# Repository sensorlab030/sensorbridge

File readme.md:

# Sensor Bridge

The sensor bridge board is a small piece of embedded hardware that allows the 
user to easily connect up to six analog sensors. The board will then read the 
data from the sensors and send this data via the serial port to a [client 
application](https://github.com/sensorlab030/sensorbridge-client) which then
either records the data to files or serves it over a websocket to interested
applications.

The firmware (/firmware) of the sensor board is [Arduino](https://www.arduino.cc/) 
based and the board layout files (/hardware) are created with 
[CadSoft/Autodesk Eagle](http://www.autodesk.com/products/eagle/overview)

## Protocol

The data from the sensors is sent over the serial port at a baud rate of 9600 
bps. 

The serial protocol in which the data is communicated is very straighforward: 
it will always send six two-byte (16 bit) values (ordered from sensor one to 
sensor six), separated by a carriage return (```0x0D```) and a line feed 
(```0x0A```). So one single message will always be 14 bytes long and  be ordered 
like this:

```
Sensor 1 value | Sensor 2 value | Sensor 3 value | Sensor 4 value |
Sensor 5 value | Sensor 5 value | Carriage return | Line feed
```

The sensor readings will have a value from 0 to 1023 (10 bit), and will be 
sent with the high byte first. If it is detected that there is no sensor 
connected to the analog input, a value of ```FF:FF``` will be sent to notify the 
disconnected state of the sensor.

### Example 1: One sensor connected, analog value of 0

This is the message that is sent when only the first sensor is connected that
has a sensor reading of 0 (```00:00```).

```
00:00:FF:FF:FF:FF:FF:FF:FF:FF:FF:FF:0D:0A
```

### Example 2: One sensor connected, analog value of 1023

This is the message that is sent when only the first sensor is connected that
has a sensor reading of 1023 (```03:FF```).

```
03:FF:FF:FF:FF:FF:FF:FF:FF:FF:FF:FF:0D:0A
```

## License

The firmware (everything under /firmware) is licensed under the GPLv3, the 
Arduino core libraries and IDE are under their own respective licenses (GNU 
LGPL and GNU GPL). License text can be found under /firmware/license.txt

The board layout files (everything under /hardware) is under the Creative 
Commons Attribution-ShareAlike 3.0 Unported License. License text can be 
found under /hardware/license.txt

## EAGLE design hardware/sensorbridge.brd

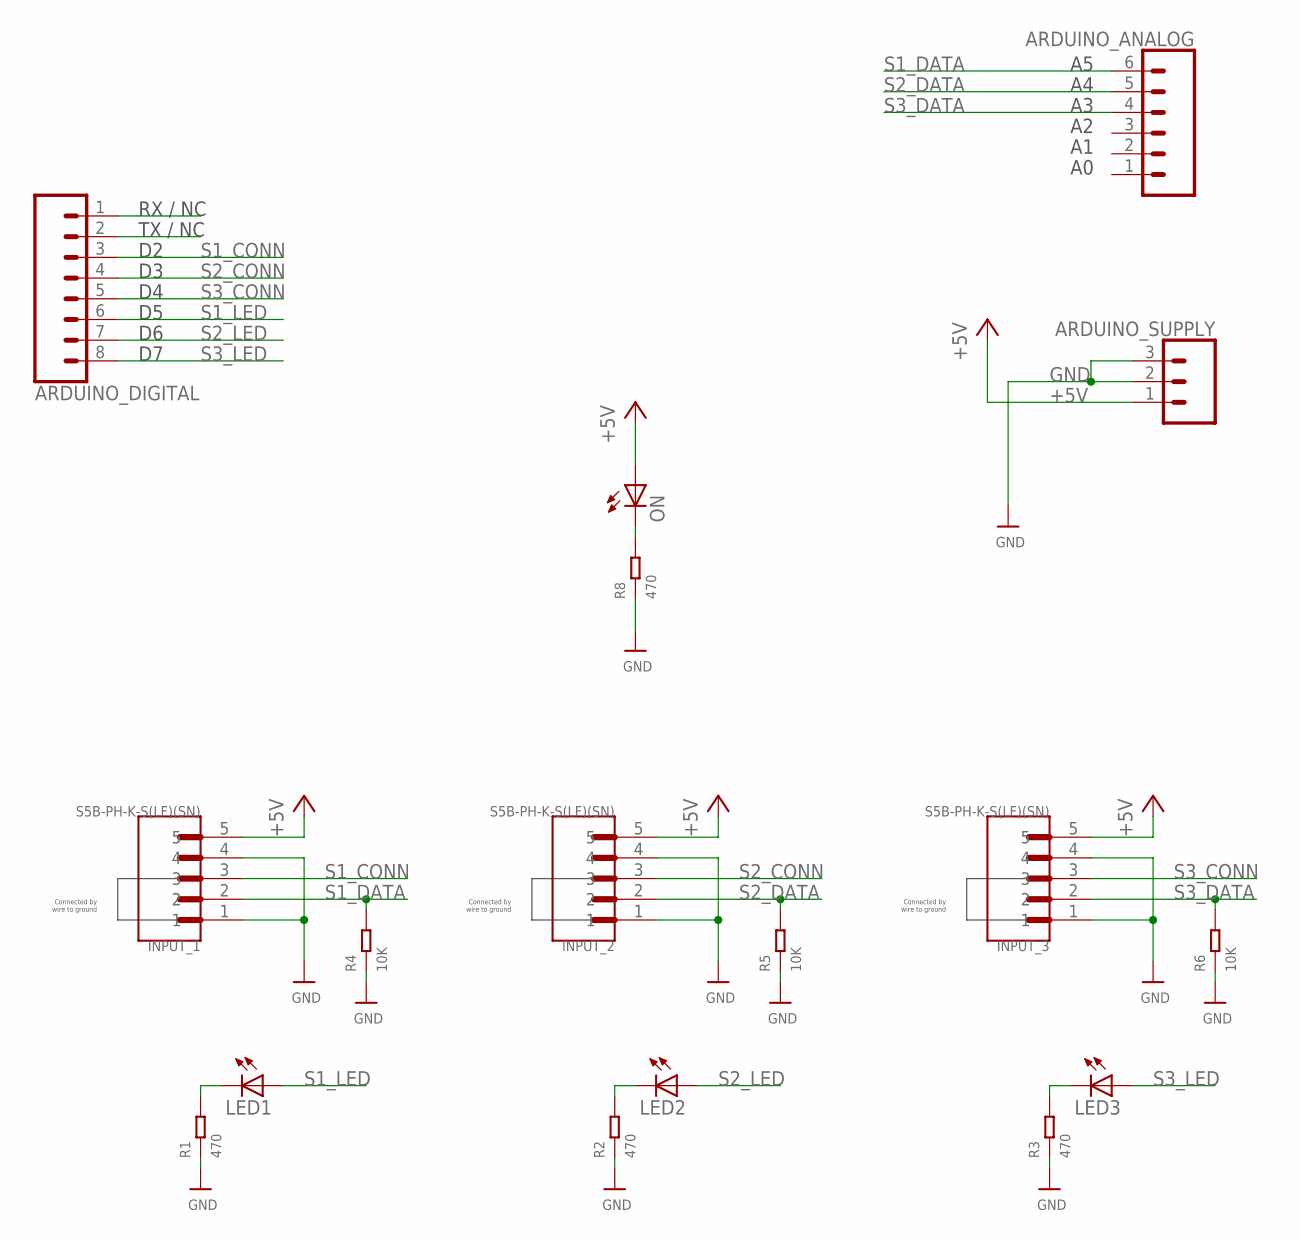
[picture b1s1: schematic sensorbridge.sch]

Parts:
ARDUINO_ANALOG: CONN_06NO_SILK_FEMALE_PTH; 1X06_NO_SILK
ARDUINO_DIGITAL: CONN_08NO_SILK_FEMALE_PTH; 1X08_NO_SILK
ARDUINO_SUPPLY: CONN_031X03_NO_SILK; 1X03_NO_SILK
INPUT_1, INPUT_2, INPUT_3: S5B-PH-K-S(LF)(SN); JST_S5B-PH-K-S(LF)(SN)
LED1, LED2, LED3: LEDCHIP-LED0603; CHIP-LED0603
ON: LEDCHIP-LED0603; CHIP-LED0603
R1, R2, R3, R8: 470; R0603
R4, R5, R6: 10K; R0603

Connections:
+5V: ARDUINO_SUPPLY.1, INPUT_1.5, INPUT_2.5, INPUT_3.5, ON.A
GND: ARDUINO_SUPPLY.2, ARDUINO_SUPPLY.3, INPUT_1.1, INPUT_1.4, INPUT_2.1, INPUT_2.4, INPUT_3.1, INPUT_3.4, R1.1, R2.1, R3.1, R4.1, R5.1, R6.1, R8.1
unnamed: LED1.C, R1.2
unnamed: LED2.C, R2.2
unnamed: LED3.C, R3.2
unnamed: ON.C, R8.2
S1_CONN: ARDUINO_DIGITAL.3, INPUT_1.3
S1_DATA: ARDUINO_ANALOG.6, INPUT_1.2, R4.2
S1_LED: ARDUINO_DIGITAL.6, LED1.A
S2_CONN: ARDUINO_DIGITAL.4, INPUT_2.3
S2_DATA: ARDUINO_ANALOG.5, INPUT_2.2, R5.2
S2_LED: ARDUINO_DIGITAL.7, LED2.A
S3_CONN: ARDUINO_DIGITAL.5, INPUT_3.3
S3_DATA: ARDUINO_ANALOG.4, INPUT_3.2, R6.2
S3_LED: ARDUINO_DIGITAL.8, LED3.A

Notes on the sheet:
RX / NC
TX / NC
Connected by wire to ground

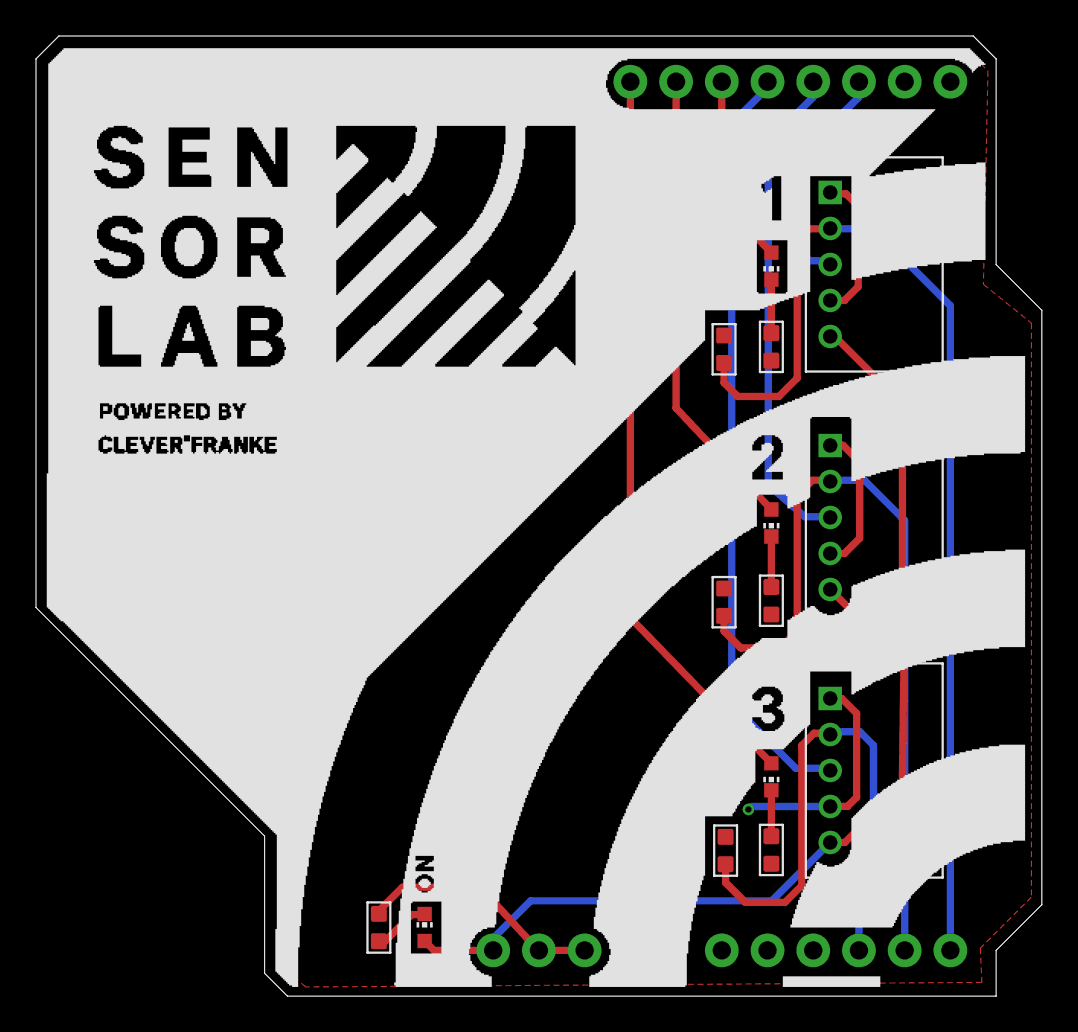
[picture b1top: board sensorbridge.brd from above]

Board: 2 copper layers, 55.9 x 53.3 mm, 17 parts (0 on the bottom side), 15 nets.

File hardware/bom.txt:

Part               Description                            Value              Octopart link
ARDUINO_ANALOG     1x6 0.1 inch male header               NA                 https://octopart.com/22-28-4090-molex-278177
ARDUINO_DIGITAL    1x8 0.1 inch male header               NA                 https://octopart.com/22-28-4090-molex-278177
ARDUINO_SUPPLY     1x3 0.1 inch male header               NA                 https://octopart.com/22-28-4090-molex-278177
INPUT_1            JST 5 position 2mm Pitch connector     NA                 https://octopart.com/s5b-ph-k-s%28lf%29%28sn%29-jst-248886
INPUT_2            JST 5 position 2mm Pitch connector     NA                 https://octopart.com/s5b-ph-k-s%28lf%29%28sn%29-jst-248886
INPUT_3            JST 5 position 2mm Pitch connector     NA                 https://octopart.com/s5b-ph-k-s%28lf%29%28sn%29-jst-248886
LED1               0603 LED (green)                       NA                 https://octopart.com/sml-d12m8wt86-rohm-8992277
LED2               0603 LED (green)                       NA                 https://octopart.com/sml-d12m8wt86-rohm-8992277
LED3               0603 LED (green)                       NA                 https://octopart.com/sml-d12m8wt86-rohm-8992277
PWR_LED            0603 LED (green)                       NA                 https://octopart.com/sml-d12m8wt86-rohm-8992277
R1                 0603 resistor                          470                https://octopart.com/cr0603-fx-4700elf-bourns-3825414
R2                 0603 resistor                          470                https://octopart.com/cr0603-fx-4700elf-bourns-3825414
R3                 0603 resistor                          470                https://octopart.com/cr0603-fx-4700elf-bourns-3825414
R4                 0603 resistor                          10K                https://octopart.com/cr0603-fx-1002elf-bourns-2326648
R5                 0603 resistor                          10K                https://octopart.com/cr0603-fx-1002elf-bourns-2326648
R6                 0603 resistor                          10K                https://octopart.com/cr0603-fx-1002elf-bourns-2326648
R8                 0603 resistor                          470                https://octopart.com/cr0603-fx-4700elf-bourns-3825414

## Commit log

2017-05-01 Added protocol to readme
2017-05-01 Updated style of hex chars in protocol
2017-05-01 Updated readme with links
2017-05-01 Fixed link in readme
2017-05-02 Added initial hardware files
2017-05-02 Updated board layout, replaced jack, added status led
2017-05-03 Adapted shield outline
2017-05-03 Added power led
2017-05-03 Added arduino pin names to info layer
2017-05-03 Added new initial firmware, reading the analog inputs, as well as the digital inputs
2017-05-03 Digital pin reconfiguration
2017-05-03 Tweaked board dimensions
2017-05-03 Replaced header parts for headers with silkscreen
2017-05-17 Added top and bottom silks
2017-05-17 Added ground planes, fixed DRC errors (dirtypcb)
2017-05-17 Replaced connectors with no-silk versions
2017-05-18 Updated silks, clearing the vias
2017-07-31 Changed connectors, made LED pin-controlled
2017-08-15 Made sensor connection through GND instead of VCC, added pulldown resistors to DATA lines
2017-08-16 Fixed DRC error
2017-08-17 Updated firmware to three sensors, added animation

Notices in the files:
parts and their libraries:
SparkFun-Connectors: Licensing: Creative Commons ShareAlike 4.0 International - https://creativecommons.org/licenses/by-sa/4.0
